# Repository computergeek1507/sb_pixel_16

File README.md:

# SBPixel16

A 16-port WS2812 pixel controller built on the **ESP32-P4**. It drives all 16 LED
strips simultaneously using the ESP32-P4's PARLIO peripheral for glitch-free parallel
DMA output. Pixel data comes from Ethernet (E1.31/sACN or DDP) or from **FSEQ
sequences played off a microSD card** in a standalone loop.

> **⚠️ WIP — Do not use.** Both the hardware and firmware are under active
> development and have not been fully validated.

This repository contains both the open-source **hardware** (KiCad 10) and the
**firmware** (Arduino / ESP-IDF).

---

## Features

- **16 parallel pixel outputs** — all strips clocked out together via PARLIO DMA,
  no RMT channel juggling.
- **Network input** — E1.31 (sACN, UDP 5568) or DDP (UDP 4048), selectable at runtime.
- **Standalone FSEQ playback** — plays uncompressed FSEQ v2 sequences (full or sparse)
  from a microSD card, looping the whole `/sequences` folder forever. No network needed.
- **Single-universe DMX512 output** — optional, generated on UART1 (250 kbaud, 8N2).
- **Web UI + REST API** — configure network, protocol, and per-port settings from a
  browser; config persists in LittleFS as `/config.json`.
- **On-OLED network setup** — set DHCP / static IP / gateway from the front-panel
  buttons, no computer required.
- **Over-the-air updates** — firmware and filesystem images can be flashed from the web UI.
- **Per-port configuration** — pixel count, start channel, color order, brightness,
  null/sacrificial pixels, and pixel grouping.
- **On-board 128×64 SSD1306 OLED** — shows IP, protocol, FPS, packet count, input
  voltages, SD status, and the currently playing sequence.
- **Two input-voltage monitors** — oversampled ADC readings (V1/V2) shown on the OLED.
- **Built-in test patterns** — cycle red / green / blue / rainbow with the on-board
  buttons; power-up RGB self-test on every boot.

---

## Repository layout

```
.
├── firmware/SBPixel16/     Arduino sketch (ESP32-P4)
│   ├── SBPixel16.ino        main app: setup/loop, config, Ethernet, parsers
│   ├── SBPixel16.h          board pin map & config structs
│   ├── parlio_ws2812.h      PARLIO parallel WS2812 DMA driver
│   ├── dmx_output.h         single-universe DMX512 output
│   ├── fseq_player.h        microSD FSEQ v2 player (uncompressed/sparse)
│   ├── net_menu.h           two-button OLED network editor
│   ├── data/                web UI source (packed into the LittleFS image)
│   └── page_*.h             web UI pages + REST API handlers
├── hardware/                KiCad 10 project (schematics, PCB, libraries)
│   └── ESP32-P4_16.*        board design files
└── LICENSE                  CC BY-NC 4.0 (firmware)
```

---

## Firmware

### Target

- **Board:** ESP32-P4 (Arduino-ESP32 3.x), e.g. Waveshare ESP32-P4-ETH
- **Ethernet PHY:** IP101GRI (RMII)
- **microSD:** the module's SDIO slot (4-bit) — used for FSEQ playback
- **Partition:** Default 4MB with SPIFFS (1.2 MB app / 1.5 MB filesystem)

### Required libraries

Install via the Arduino Library Manager:

| Library | Source |
| --- | --- |
| ESPAsyncWebServer | github.com/ESP32Async/ESPAsyncWebServer |
| AsyncTCP | github.com/ESP32Async/AsyncTCP |
| ArduinoJson | arduinojson.org |
| Adafruit GFX + Adafruit SSD1306 | Adafruit (OLED display) |

### Build & flash

1. Install the ESP32 board package (Arduino-ESP32 **3.x**) and select an **ESP32-P4** board.
2. **Enable PSRAM** (Tools → PSRAM → *Enabled* = `-DBOARD_HAS_PSRAM`). The module has
   PSRAM but the board default is *Disabled*, which leaves it uninitialized.
3. Set the partition scheme to **Default 4MB with SPIFFS**.
4. Open `firmware/SBPixel16/SBPixel16.ino`, compile, and upload.
5. Upload the web UI: flash the LittleFS filesystem image — a prebuilt
   `SBPixel16.littlefs.bin` is provided, or re-flash it over the air from the web UI.

On first boot with no `/config.json`, the firmware writes sensible defaults
(DHCP on, E1.31, 100 pixels/port, RGB order, 30% brightness).

**Board revisions:** the default build targets **HW1** (original pin map). Build for
the revised **HW2** board (pixel ports 12–16 rerouted off the USB pins onto
GPIO32/33/46/47/48) with `-DHW_VERSION=2`.

**Prebuilt binaries:** every push builds HW1 + HW2 firmware and the KiCad fabrication
outputs in CI — download them from the repo's **Actions** tab. When flashing over
serial after an OTA, use the `.merged.bin` (or first `esptool erase-region 0xe000
0x2000`), otherwise the bootloader keeps booting the previous OTA partition.

### REST API

| Method | Endpoint | Purpose |
| --- | --- | --- |
| GET | `/api/status` | Runtime stats (FPS, packet counts, voltages, SD/FSEQ status) |
| GET | `/api/config` | Current configuration as JSON |
| POST | `/api/config` | Update configuration |
| POST | `/api/reboot` | Reboot the controller |
| POST | `/api/ota/firmware` | Upload a firmware image |
| POST | `/api/ota/filesystem` | Upload a filesystem (web UI) image |

### Key defaults

- Refresh rate: ~40 fps (25 ms frame interval)
- Max pixels per port: 340 (configurable in `SBPixel16.h`)
- Input protocols: `0` = E1.31, `1` = DDP, `2` = FSEQ (SD card)
- Data timeout: outputs blank after 1 s with no packets
- E1.31 UDP port 5568 · DDP UDP port 4048 · HTTP port 80

### Front-panel controls (two buttons)

| Button | Action |
| --- | --- |
| **BTN1** tap | Cycle test pattern: Off → Red → Green → Blue → Rainbow → Off |
| **BTN2** tap | Stop the test pattern |
| **BTN2** hold (~1.5 s) | Open the `NETWORK SETUP` menu on the OLED |

**In the network menu:** **BTN1** changes the value under the cursor (hold to
auto-repeat), **BTN2** advances to the next field. Order: DHCP on/off → IP →
gateway → *Save & reboot*. Saving writes the config and reboots; 30 s of inactivity
cancels. Lets you set a static IP without a computer.

### FSEQ playback (microSD)

The microSD card is mounted at boot in every mode — its status shows on the OLED
(a card icon in the header) and the web dashboard. Set the input protocol to **FSEQ**
(Network page, or `protocol: 2`) to play from it: the controller scans **`/sequences`**
for `*.fseq` files, plays them alphabetically, and loops the whole folder forever — no
network connection required.

- **Format:** FSEQ v2, **uncompressed only** (full or sparse frames). Export from
  xLights / FPP with *No Compression*. Compressed files are skipped.
- **Channel mapping:** frame channels map to ports by each port's **Start Ch.**, exactly
  like E1.31/DDP — so brightness, color order, and grouping all still apply.
- The OLED and the web dashboard show the mounted card and the sequence now playing.

---

## Hardware

The board is a KiCad 10 open-hardware design (`hardware/ESP32-P4_16.*`) with 16 buffered
pixel outputs, dual power inputs with voltage monitoring, an SSD1306 OLED, two buttons,
and RMII Ethernet.

Design files, interactive BOM, and part list are published on the upstream project:

- **Interactive BOM:** https://computergeek1507.github.io/PB_16/ESP32-P4_16/bom/ibom
- **Part BOM (.ods):** https://github.com/computergeek1507/PB_16/raw/master/ESP32-P4_16/ESP32-P4_16_BOM.ods

---

## Licensing

Both the **firmware** and the **hardware** are licensed under **CC BY-NC 4.0**
(see [LICENSE](LICENSE)) — free to share and adapt for non-commercial use with
attribution.

Copyright © 2025 Scott Hanson.

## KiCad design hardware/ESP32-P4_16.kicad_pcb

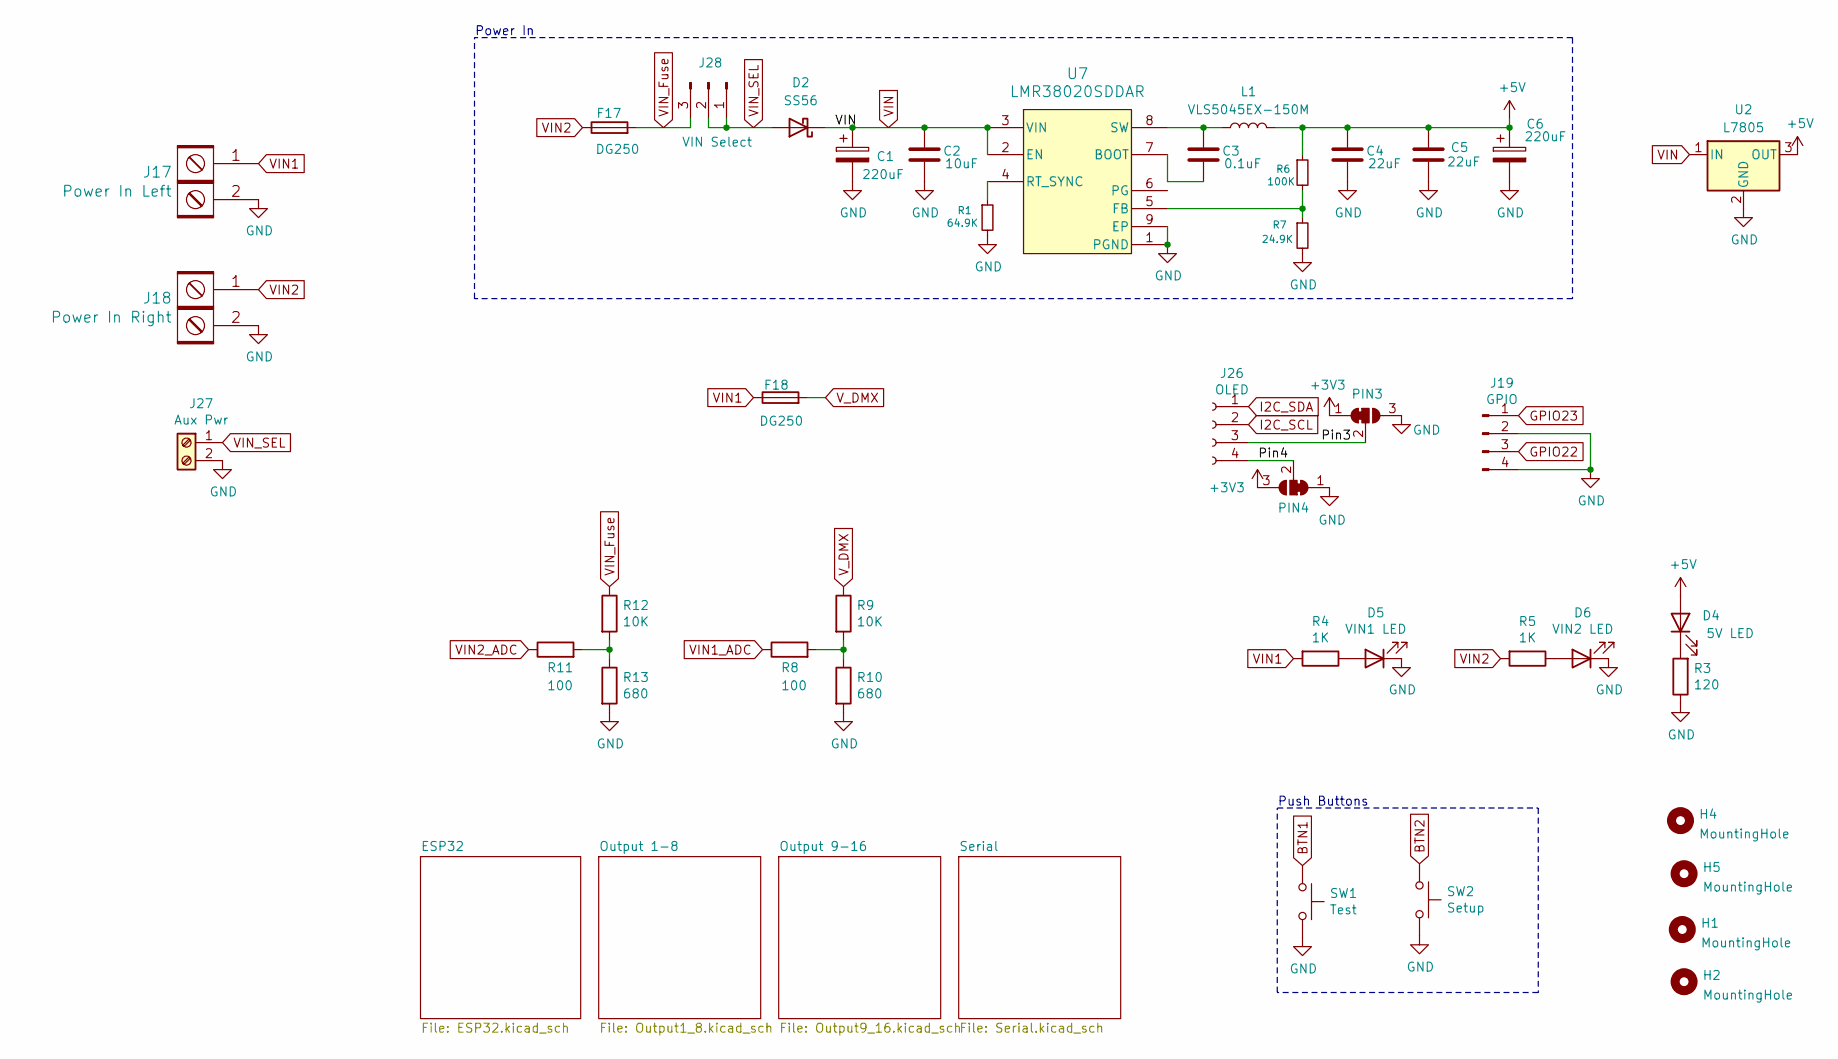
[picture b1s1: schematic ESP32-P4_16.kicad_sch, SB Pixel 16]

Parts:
C1, C6: 220uF; CP_Elec_8x10.5; LCSC C3340
C2: 10uF; C_1206_3216Metric; LCSC_PN C13585
C3: 0.1uF; C_0603_1608Metric; MPN CC0603KRX7R9BB104; LCSC C14663
C4, C5: 22uF; C_1206_3216Metric; LCSC_PN C1859
D2: SS56; D_SMA; LCSC C65009
D4: 5V LED; LED_0603_1608Metric; MPN LTST-C190KRKT; Digi-Key_PN 160-1436-2-ND
D5: VIN1 LED; LED_0603_1608Metric; MPN LTST-C190KRKT; Digi-Key_PN 160-1436-2-ND
D6: VIN2 LED; LED_0603_1608Metric; MPN LTST-C190KRKT; Digi-Key_PN 160-1436-2-ND
F17: DG250; Fuse_1812_4532Metric; MPN 3544-2
F18: DG250; Fuse_1812_4532Metric
H1, H2, H4, H5: MountingHole; MountingHole_3.7mm
J17: Power In Left; BARRIER_BLOCK_1ROW_2POS_P9.5MM; MPN OSTYK51102030; Digi-Key_PN ED2953-ND
J18: Power In Right; BARRIER_BLOCK_1ROW_2POS_P9.5MM; MPN OSTYK51102030; Digi-Key_PN ED2953-ND
J19: GPIO; JST_XH_B4B-XH-A_1x04_P2.50mm_Vertical; MPN B4B-XH-A(LF)(SN); Digi-Key_PN 455-2249-ND
J26: OLED; OLED-SSD1306-128X64-I2C-THT_2HOLE; MPN PPTC041LFBN-RC; Digi-Key_PN S7002-ND
J27: Aux Pwr; PHOENIX_MKDS1_2-3.81; MPN 1727010; Digi-Key_PN 277-1947-ND
J28: VIN Select; PinHeader_1x03_P2.54mm_Vertical; MPN 61300311121; Digi-Key_PN 732-5316-ND
L1: VLS5045EX-150M; IND_VLS5045EX-150M; MPN VLS5045EX-150M; Digi-Key_PN 445-174845-1-ND
PIN3: Jumper; SolderJumper-3_P1.3mm_Bridged12_Pad1.0x1.5mm
PIN4: JUMPER; SolderJumper-3_P1.3mm_Bridged12_Pad1.0x1.5mm
R1: 64.9K; R_0603_1608Metric; LCSC C14891
R3: 120; R_0603_1608Metric; MPN CRGCQ0603F120R; Digi-Key_PN A129677CT-ND
R4, R5: 1K; R_0603_1608Metric; MPN RC0603FR-071KL; Digi-Key_PN 311-1.00KHRTR-ND
R6: 100K; R_0603_1608Metric; LCSC C25803
R7: 24.9K; R_0603_1608Metric; LCSC C25962
R8, R11: 100; R_0603_1608Metric; MPN RMCF0603FT100R; Digi-Key_PN RMCF0603FT100RCT-ND
R9, R12: 10K; R_0603_1608Metric; MPN RC0603FR-0710KL; Digi-Key_PN 311-10.0KHRCT-ND
R10, R13: 680; R_0603_1608Metric; MPN RC0603FR-07680RL; Digi-Key_PN 311-680HRCT-ND
SW1: Test; SW_Push_1P1T_NO_6x6mm_H9.5mm; MPN PTS645SL50SMTR92 LFS; Digi-Key_PN CKN9088CT-ND
SW2: Setup; SW_Push_1P1T_NO_6x6mm_H9.5mm; MPN PTS645SL50SMTR92 LFS; Digi-Key_PN CKN9088CT-ND
U2: L7805; OKI-78SR_Horz
U7: LMR38020SDDAR; DDA0008E-IPC_A; MPN LMR38020SDDAR; Digi-Key_PN 296-LMR38020SDDARCT-ND

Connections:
+3V3: PIN3.1 (A), PIN4.3 (B); also elsewhere on the board
+5V: C4.1, C5.1, C6.1, D4.2 (A), L1.2, R6.1, U2.3 (OUT); also elsewhere on the board
/Pin3: J26.3, PIN3.2 (C)
/Pin4: J26.4, PIN4.2 (C)
BTN1: SW1.1; also elsewhere on the board
BTN2: SW2.1; also elsewhere on the board
GND: C1.2, C2.2, C4.2, C5.2, C6.2, D5.1 (K), D6.1 (K), J17.2, J18.2, J19.2, J19.4, J27.2, PIN3.3 (B), PIN4.1 (A), R1.2, R3.1, R7.2, R10.2, R13.2, SW1.2, SW2.2, U2.2 (GND), U7.1 (PGND), U7.9 (EP); also elsewhere on the board
GPIO22: J19.3; also elsewhere on the board
GPIO23: J19.1; also elsewhere on the board
I2C_SCL: J26.2; also elsewhere on the board
I2C_SDA: J26.1; also elsewhere on the board
unnamed: D4.1 (K), R3.2
unnamed: D5.2 (A), R4.1
unnamed: D6.2 (A), R5.1
unnamed: R8.2, R9.2, R10.1
unnamed: R11.2, R12.2, R13.1
unnamed: C3.2, U7.7 (BOOT)
unnamed: R6.2, R7.1, U7.5 (FB)
unnamed: R1.1, U7.4 (RT_SYNC)
unnamed: C3.1, L1.1, U7.8 (SW)
VIN: C1.1, C2.1, D2.1 (K), U2.1 (IN), U7.2 (EN), U7.3 (VIN)
VIN1: F18.1, J17.1, R4.2; also elsewhere on the board
VIN1_ADC: R8.1; also elsewhere on the board
VIN2: F17.1, J18.1, R5.2; also elsewhere on the board
VIN2_ADC: R11.1; also elsewhere on the board
VIN_Fuse: F17.2, J28.3, R12.1
VIN_SEL: D2.2 (A), J27.1, J28.1, J28.2
V_DMX: F18.2, R9.1; also elsewhere on the board

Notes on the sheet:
Push Buttons
Power In

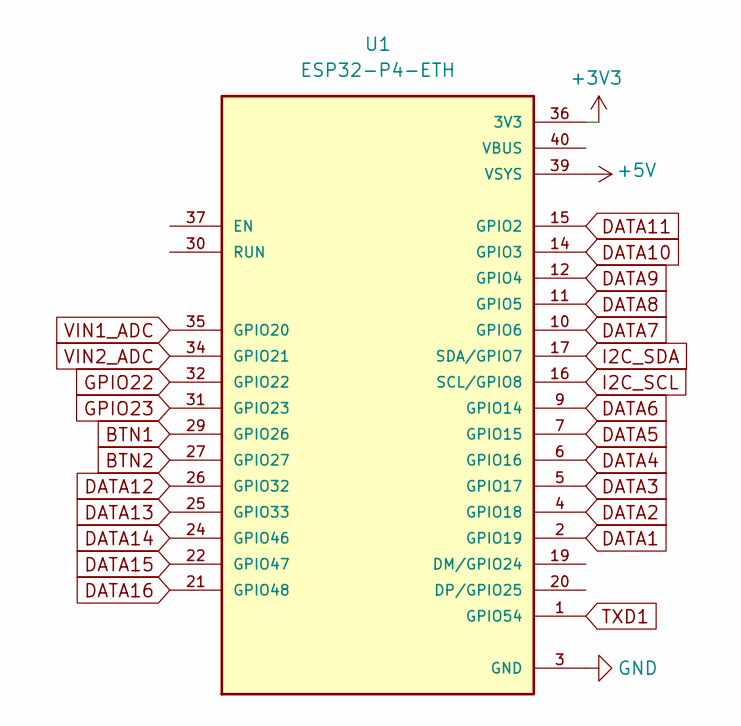
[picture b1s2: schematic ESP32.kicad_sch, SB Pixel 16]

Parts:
U1: ESP32-P4-ETH; MODULE_ESP32-P4-ETH

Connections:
+3V3: U1.36 (3V3); also elsewhere on the board
+5V: U1.39 (VSYS); also elsewhere on the board
BTN1: U1.29 (GPIO26); also elsewhere on the board
BTN2: U1.27 (GPIO27); also elsewhere on the board
DATA1: U1.2 (GPIO19); also elsewhere on the board
DATA2: U1.4 (GPIO18); also elsewhere on the board
DATA3: U1.5 (GPIO17); also elsewhere on the board
DATA4: U1.6 (GPIO16); also elsewhere on the board
DATA5: U1.7 (GPIO15); also elsewhere on the board
DATA6: U1.9 (GPIO14); also elsewhere on the board
DATA7: U1.10 (GPIO6); also elsewhere on the board
DATA8: U1.11 (GPIO5); also elsewhere on the board
DATA9: U1.12 (GPIO4); also elsewhere on the board
DATA10: U1.14 (GPIO3); also elsewhere on the board
DATA11: U1.15 (GPIO2); also elsewhere on the board
DATA12: U1.26 (GPIO32); also elsewhere on the board
DATA13: U1.25 (GPIO33); also elsewhere on the board
DATA14: U1.24 (GPIO46); also elsewhere on the board
DATA15: U1.22 (GPIO47); also elsewhere on the board
DATA16: U1.21 (GPIO48); also elsewhere on the board
GND: U1.3 (GND), U1.8 (GND), U1.13 (GND), U1.18 (GND), U1.23 (GND), U1.28 (GND), U1.33 (GND), U1.38 (GND); also elsewhere on the board
GPIO22: U1.32 (GPIO22); also elsewhere on the board
GPIO23: U1.31 (GPIO23); also elsewhere on the board
I2C_SCL: U1.16 (SCL/GPIO8); also elsewhere on the board
I2C_SDA: U1.17 (SDA/GPIO7); also elsewhere on the board
TXD1: U1.1 (GPIO54); also elsewhere on the board
VIN1_ADC: U1.35 (GPIO20); also elsewhere on the board
VIN2_ADC: U1.34 (GPIO21); also elsewhere on the board

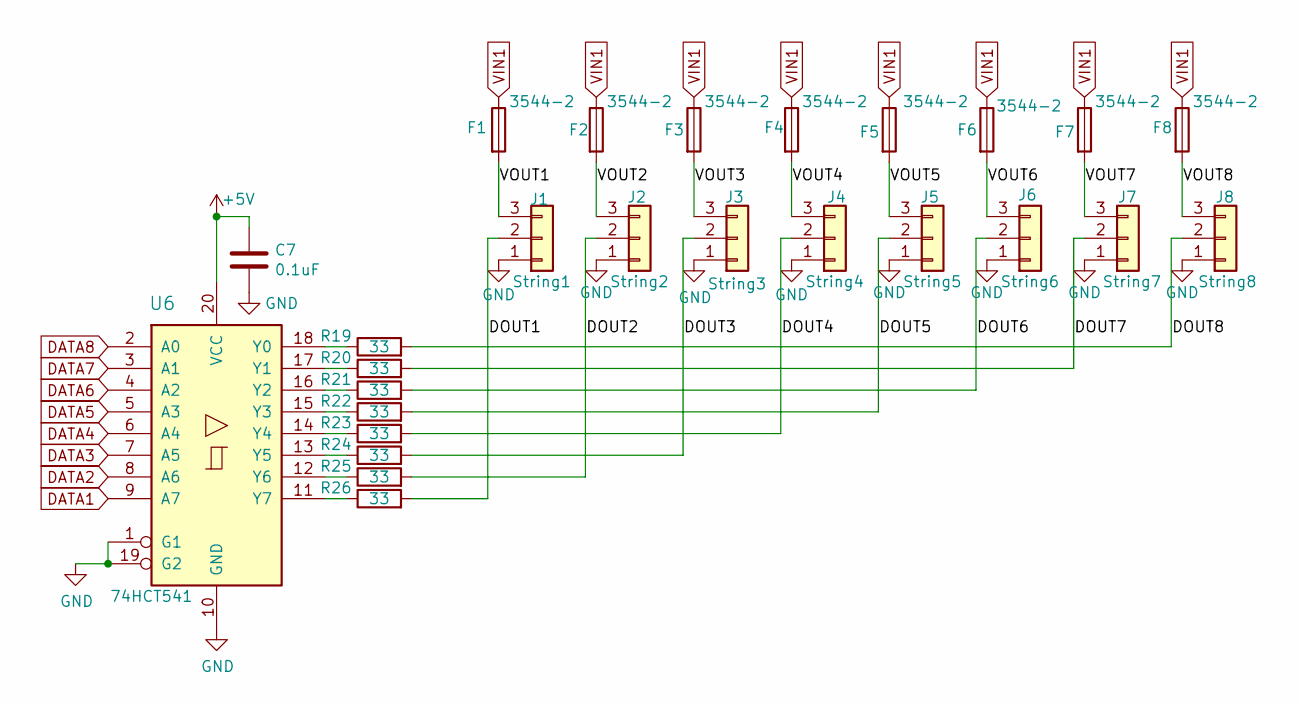
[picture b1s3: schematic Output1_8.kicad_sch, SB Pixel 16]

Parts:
C7: 0.1uF; C_0603_1608Metric; MPN CL10B104KB8NNWC; Digi-Key_PN 1276-1935-2-ND
F1, F2, F3, F4, F5, F6, F7, F8: 3544-2; Fuse_1812_4532Metric; MPN 3544-2
J1: String1; PHOENIX_1864299_1; MPN 1843619/OSTTJ0311530
J2: String2; PHOENIX_1864299_1; MPN 1843619/OSTTJ0311530
J3: String3; PHOENIX_1864299_1; MPN 1843619/OSTTJ0311530
J4: String4; PHOENIX_1864299_1; MPN 1843619/OSTTJ0311530
J5: String5; PHOENIX_1864299_1; MPN 1843619/OSTTJ0311530
J6: String6; PHOENIX_1864299_1; MPN 1843619/OSTTJ0311530
J7: String7; PHOENIX_1864299_1; MPN 1843619/OSTTJ0311530
J8: String8; PHOENIX_1864299_1; MPN 1843619/OSTTJ0311530
R19, R20, R21, R22, R23, R24, R25, R26: 33; R_0603_1608Metric; MPN CN34J330CT; LCSC C23140
U6: 74HCT541; TSSOP-20_4.4x6.5mm_P0.65mm; MPN SN74HCT541PWR; Digi-Key_PN MC74HCT541ADTR2GOSTR-ND

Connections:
+5V: C7.1, U6.20 (VCC); also elsewhere on the board
/Output 1-8/DOUT1: J1.2, R26.2
/Output 1-8/DOUT2: J2.2, R25.2
/Output 1-8/DOUT3: J3.2, R24.2
/Output 1-8/DOUT4: J4.2, R23.2
/Output 1-8/DOUT5: J5.2, R22.2
/Output 1-8/DOUT6: J6.2, R21.2
/Output 1-8/DOUT7: J7.2, R20.2
/Output 1-8/DOUT8: J8.2, R19.2
/Output 1-8/VOUT1: F1.2, J1.3
/Output 1-8/VOUT2: F2.2, J2.3
/Output 1-8/VOUT3: F3.2, J3.3
/Output 1-8/VOUT4: F4.2, J4.3
/Output 1-8/VOUT5: F5.2, J5.3
/Output 1-8/VOUT6: F6.2, J6.3
/Output 1-8/VOUT7: F7.2, J7.3
/Output 1-8/VOUT8: F8.2, J8.3
DATA1: U6.9 (A7); also elsewhere on the board
DATA2: U6.8 (A6); also elsewhere on the board
DATA3: U6.7 (A5); also elsewhere on the board
DATA4: U6.6 (A4); also elsewhere on the board
DATA5: U6.5 (A3); also elsewhere on the board
DATA6: U6.4 (A2); also elsewhere on the board
DATA7: U6.3 (A1); also elsewhere on the board
DATA8: U6.2 (A0); also elsewhere on the board
GND: C7.2, J1.1, J2.1, J3.1, J4.1, J5.1, J6.1, J7.1, J8.1, U6.1 (G1), U6.10 (GND), U6.19 (G2); also elsewhere on the board
unnamed: R19.1, U6.18 (Y0)
unnamed: R20.1, U6.17 (Y1)
unnamed: R21.1, U6.16 (Y2)
unnamed: R22.1, U6.15 (Y3)
unnamed: R23.1, U6.14 (Y4)
unnamed: R24.1, U6.13 (Y5)
unnamed: R25.1, U6.12 (Y6)
unnamed: R26.1, U6.11 (Y7)
VIN1: F1.1, F2.1, F3.1, F4.1, F5.1, F6.1, F7.1, F8.1; also elsewhere on the board

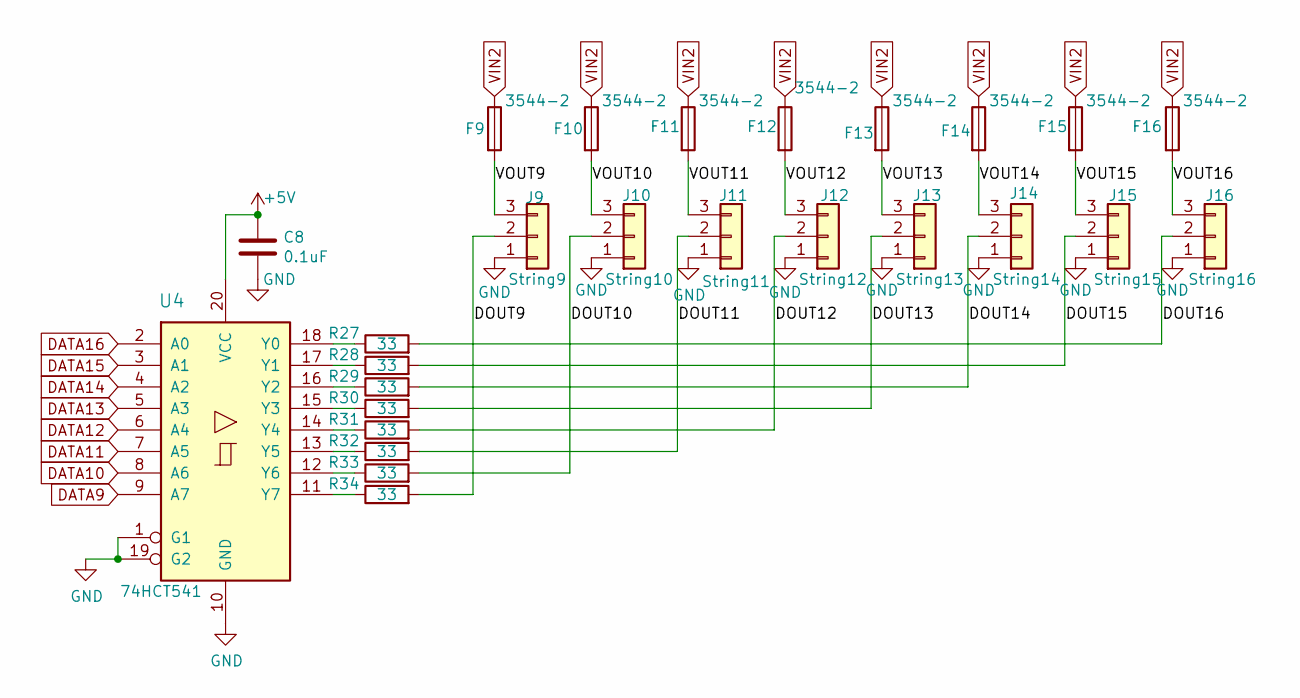
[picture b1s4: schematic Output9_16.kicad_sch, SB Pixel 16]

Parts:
C8: 0.1uF; C_0603_1608Metric; MPN CL10B104KB8NNWC; Digi-Key_PN 1276-1935-2-ND
F9, F10, F11, F12, F13, F14, F15, F16: 3544-2; Fuse_1812_4532Metric; MPN 3544-2
J9: String9; PHOENIX_1864299_1; MPN 1843619/OSTTJ0311530
J10: String10; PHOENIX_1864299_1; MPN 1843619/OSTTJ0311530
J11: String11; PHOENIX_1864299_1; MPN 1843619/OSTTJ0311530
J12: String12; PHOENIX_1864299_1; MPN 1843619/OSTTJ0311530
J13: String13; PHOENIX_1864299_1; MPN 1843619/OSTTJ0311530
J14: String14; PHOENIX_1864299_1; MPN 1843619/OSTTJ0311530
J15: String15; PHOENIX_1864299_1; MPN 1843619/OSTTJ0311530
J16: String16; PHOENIX_1864299_1; MPN 1843619/OSTTJ0311530
R27, R28, R29, R30, R31, R32, R33, R34: 33; R_0603_1608Metric; MPN CN34J330CT; LCSC C23140
U4: 74HCT541; TSSOP-20_4.4x6.5mm_P0.65mm; MPN SN74HCT541PWR; Digi-Key_PN MC74HCT541ADTR2GOSTR-ND

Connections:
+5V: C8.1, U4.20 (VCC); also elsewhere on the board
/Output 9-16/DOUT9: J9.2, R34.2
/Output 9-16/DOUT10: J10.2, R33.2
/Output 9-16/DOUT11: J11.2, R32.2
/Output 9-16/DOUT12: J12.2, R31.2
/Output 9-16/DOUT13: J13.2, R30.2
/Output 9-16/DOUT14: J14.2, R29.2
/Output 9-16/DOUT15: J15.2, R28.2
/Output 9-16/DOUT16: J16.2, R27.2
/Output 9-16/VOUT9: F9.2, J9.3
/Output 9-16/VOUT10: F10.2, J10.3
/Output 9-16/VOUT11: F11.2, J11.3
/Output 9-16/VOUT12: F12.2, J12.3
/Output 9-16/VOUT13: F13.2, J13.3
/Output 9-16/VOUT14: F14.2, J14.3
/Output 9-16/VOUT15: F15.2, J15.3
/Output 9-16/VOUT16: F16.2, J16.3
DATA9: U4.9 (A7); also elsewhere on the board
DATA10: U4.8 (A6); also elsewhere on the board
DATA11: U4.7 (A5); also elsewhere on the board
DATA12: U4.6 (A4); also elsewhere on the board
DATA13: U4.5 (A3); also elsewhere on the board
DATA14: U4.4 (A2); also elsewhere on the board
DATA15: U4.3 (A1); also elsewhere on the board
DATA16: U4.2 (A0); also elsewhere on the board
GND: C8.2, J9.1, J10.1, J11.1, J12.1, J13.1, J14.1, J15.1, J16.1, U4.1 (G1), U4.10 (GND), U4.19 (G2); also elsewhere on the board
unnamed: R27.1, U4.18 (Y0)
unnamed: R28.1, U4.17 (Y1)
unnamed: R29.1, U4.16 (Y2)
unnamed: R30.1, U4.15 (Y3)
unnamed: R31.1, U4.14 (Y4)
unnamed: R32.1, U4.13 (Y5)
unnamed: R33.1, U4.12 (Y6)
unnamed: R34.1, U4.11 (Y7)
VIN2: F9.1, F10.1, F11.1, F12.1, F13.1, F14.1, F15.1, F16.1; also elsewhere on the board

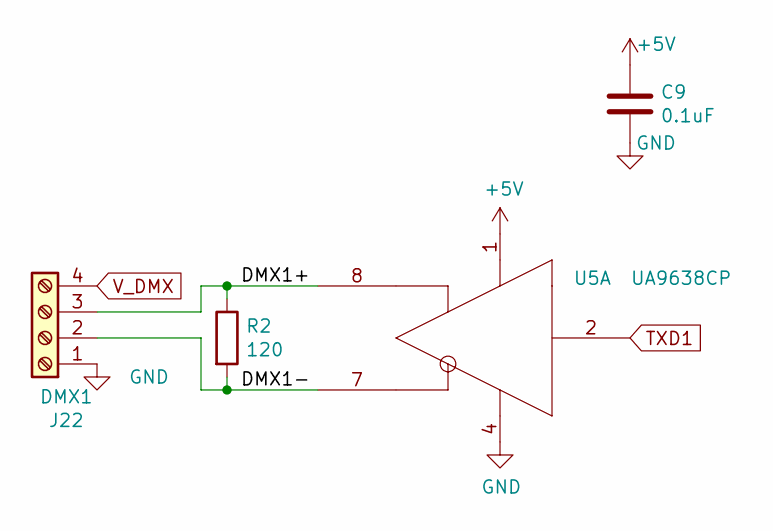
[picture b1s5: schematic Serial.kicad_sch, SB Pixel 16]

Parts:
C9: 0.1uF; C_0603_1608Metric; MPN CL10B104KB8NNWC; Digi-Key_PN 1276-1935-2-ND
J22: DMX1; TerminalBlock_Phoenix_MKDS-1,5-4_1x04_P5.00mm_Horizontal; MPN 1729034; Digi-Key_PN 277-1238-ND
R2: 120; R_0603_1608Metric; MPN CRGCQ0603F120R; Digi-Key_PN A129677CT-ND
U5: UA9638CP; SOIC-8_3.9x4.9mm_P1.27mm; MPN UA9638CDR; Digi-Key_PN UA9638CP

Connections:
+5V: C9.1, U5.1 (VCC); also elsewhere on the board
/Serial/DMX1+: J22.3, R2.1, U5.8 (OUTB)
/Serial/DMX1-: J22.2, R2.2, U5.7 (OUTA)
GND: C9.2, J22.1, U5.4 (GND); also elsewhere on the board
TXD1: U5.2 (IN); also elsewhere on the board
V_DMX: J22.4; also elsewhere on the board

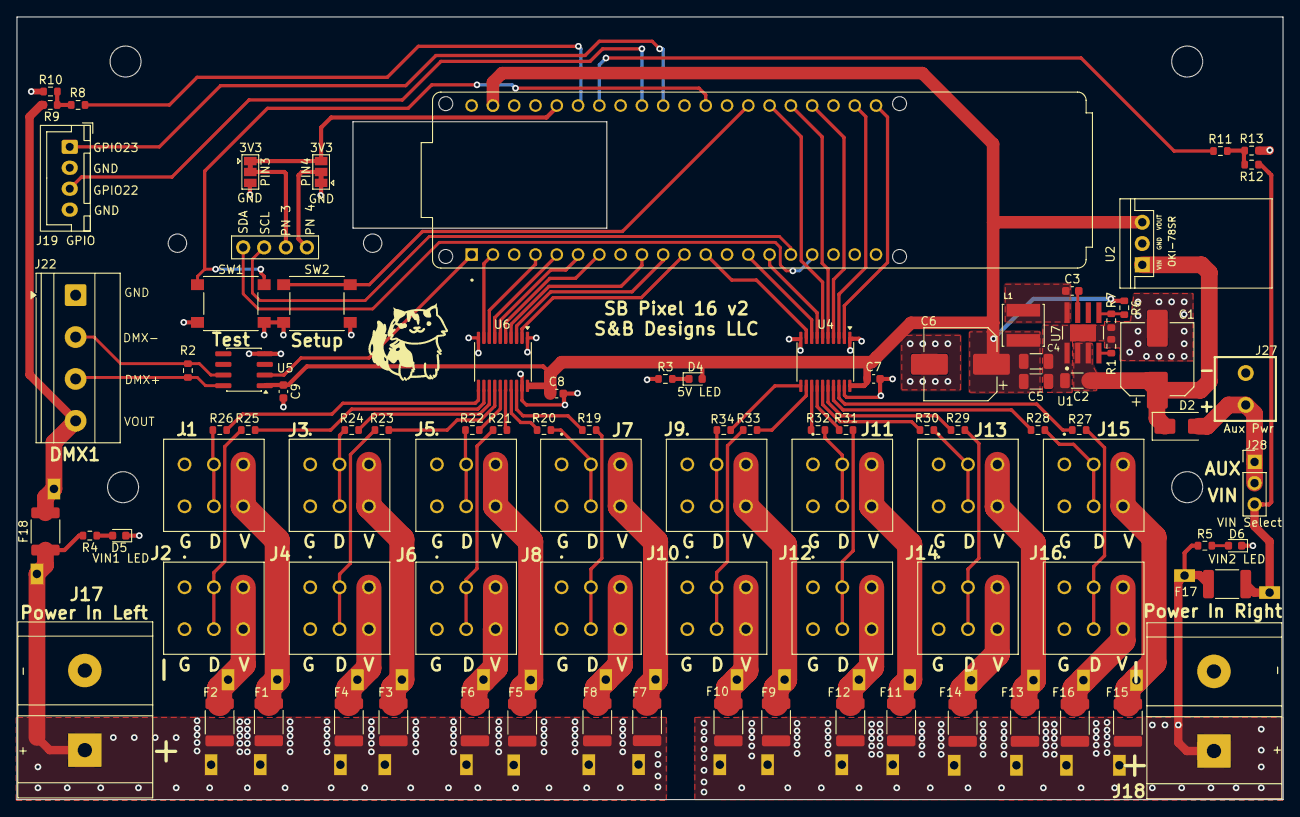
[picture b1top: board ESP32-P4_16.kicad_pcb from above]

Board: 2 copper layers, 151.1 x 93.4 mm, 98 parts (0 on the bottom side), 95 nets.

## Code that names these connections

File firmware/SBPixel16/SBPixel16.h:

#pragma once

// ── Firmware version ──────────────────────────────────────────────────────────
#define FW_VERSION    "1.0.0"                 // semantic version (bump on release)
#define FW_BUILD      17                      // build number (bump each flashed build)
#define FW_BUILD_DATE (__DATE__ " " __TIME__) // compile timestamp = unique build id

// ── Board / port constants ────────────────────────────────────────────────────

#define NUM_PORTS       16
#define MAX_PIXELS      340     // max pixels per port; increase if needed (affects FPS)
#define DATA_TIMEOUT    1000    // ms before clearing pixels on no data
#define REFRESH         25      // ms between FastLED.show() calls (~40fps target)
#define PORT_CYCLE_MS   2000    // port-cycle test: ms each port stays lit
#define HTTP_PORT       80
#define E131_UDP_PORT   5568
#define DDP_UDP_PORT    4048
#define CONFIG_FILE     "/config.json"

// ── GPIO output pins for the 16 pixel ports ───────────────────────────────────
// Pin assignments taken directly from the board schematic DATA1–DATA16 labels.
// NOTE: DATA14=GPIO24 (USB DM) and DATA16=GPIO25 (USB DP) — using these for
// pixel output disables USB on-the-fly; acceptable since USB is not needed here.
#define PIN_P0   19   // DATA1
#define PIN_P1   18   // DATA2
#define PIN_P2   17   // DATA3
#define PIN_P3   16   // DATA4
#define PIN_P4   15   // DATA5
#define PIN_P5   14   // DATA6
#define PIN_P6    6   // DATA7
#define PIN_P7    5   // DATA8
#define PIN_P8    4   // DATA9
#define PIN_P9    3   // DATA10
#define PIN_P10   2   // DATA11

// ── Board revision: pixel ports 12-16 (PIN_P11..PIN_P15) differ per HW rev ─────
// HW1 = original board.  HW2 = revised board that reroutes ports 12-16 (notably
// 14 & 16 off the USB pins GPIO24/25).  Build HW2 with -DHW_VERSION=2, or change
// the default below.
#ifndef HW_VERSION
#define HW_VERSION  1
#endif

#if HW_VERSION >= 2
  // ---- HW2 (revised board): ports 12-16 remapped off the USB pins ----
  #define PIN_P11  32   // DATA12  (port 12)  was GPIO46
  #define PIN_P12  33   // DATA13  (port 13)  was GPIO47
  #define PIN_P13  46   // DATA14  (port 14)  was GPIO24 (USB DM)
  #define PIN_P14  47   // DATA15  (port 15)  was GPIO48
  #define PIN_P15  48   // DATA16  (port 16)  was GPIO25 (USB DP)
#else
  // ---- HW1 (original board) ----
  #define PIN_P11  46   // DATA12
  #define PIN_P12  47   // DATA13
  #define PIN_P13  24   // DATA14  (USB DM — dead on HW1)
  #define PIN_P14  48   // DATA15
  #define PIN_P15  25   // DATA16  (USB DP — dead on HW1)
#endif

// ── Ethernet PHY (IP101GRI on Waveshare ESP32-P4-ETH) ─────────────────────────
#define ETH_PHY_TYPE    ETH_PHY_IP101
#define ETH_PHY_ADDR    1
#define ETH_PHY_MDC     31
#define ETH_PHY_MDIO    52
#define ETH_PHY_POWER   51      // PHY reset / power-enable
#define ETH_CLK_MODE    EMAC_CLK_EXT_IN  // 50 MHz ext crystal → GPIO50

// ── OLED (SSD1306 128×64, I2C) ───────────────────────────────────────────────
// Uses the Waveshare board's default I2C bus.
#define OLED_SDA    7
#define OLED_SCL    8
#define OLED_ADDR   0x3C
#define OLED_W      128
#define OLED_H      64

// ── microSD (SDIO 4-bit, on the ESP32-P4-ETH module) ──────────────────────────
// Card slot lives on the Waveshare module, not the SBPixel16 PCB. SDMMC signals:
#define SD_CLK_PIN  43
#define SD_CMD_PIN  44
#define SD_D0_PIN   39
#define SD_D1_PIN   40
#define SD_D2_PIN   41
#define SD_D3_PIN   42
#define SD_PWR_PIN  45      // Q1 high-side P-FET: drive LOW to power the card
#define FSEQ_DIR    "/sequences"   // sequences played in a loop from here
#define SD_CONFIG_FILE "/config.json"   // optional config override, SD card root

// ── ADC inputs ────────────────────────────────────────────────────────────────
#define VIN1_PIN    20   // VIN1_ADC
#define VIN2_PIN    21   // VIN2_ADC
#define ADC_SAMPLES  8   // oversampling count for noise reduction
// VIN sense divider (per schematic): VINx --[10k]-- node --[680]-- GND,
// node --[100]-- ADC pin. Actual VIN = pin_mV * (10000+680)/680.
#define VIN_DIV_NUM  10680
#define VIN_DIV_DEN  680

// ── Buttons ───────────────────────────────────────────────────────────────────
#define BTN1_PIN    26   // test-cycle button (active LOW, internal pull-up)
#define BTN2_PIN    27   // test-stop  button (active LOW, internal pull-up)
#define BTN_DEBOUNCE_MS  50
#define LONGPRESS_MS    1500   // hold BTN1 this long to open the OLED network menu
#define REPEAT_DELAY_MS  500   // hold-to-repeat: delay before auto-repeat starts
#define REPEAT_RATE_MS   120   // hold-to-repeat: interval between repeats

// ── Pixel output limits ───────────────────────────────────────────────────────
#define MAX_NULL_PIXELS  50    // max null/sacrificial pixels per port
#define MAX_GROUPING      8    // max physical LEDs per logical channel group

// ── Color order (wire order of the physical LED) ──────────────────────────────
// FastLED NEOPIXEL sends bytes as G,R,B. These constants drive the permutation
// that makes each physical LED type receive the correct byte sequence.
#define CO_GRB  0   // WS2812 / WS2811 default
#define CO_RGB  1
#define CO_BGR  2
#define CO_RBG  3
#define CO_GBR  4
#define CO_BRG  5

// ── Input protocol ────────────────────────────────────────────────────────────
#define PROTO_E131  0
#define PROTO_DDP   1
#define PROTO_FSEQ  2   // play FSEQ files from microSD in an endless loop

// ── Config structs ────────────────────────────────────────────────────────────

typedef struct {
    uint16_t pixelCount;    // logical pixel count (unique channel groups)
    uint32_t startChannel;  // absolute 1-based channel index
    uint8_t  colorOrder;    // CO_GRB … CO_BRG (default CO_GRB = 0)
    uint8_t  nullPixels;    // sacrificial pixels sent before data (0–MAX_NULL_PIXELS)
    uint8_t  grouping;      // physical LEDs per logical pixel (1 = no grouping)
    uint8_t  brightness;    // per-port output brightness, percent (0-100)
} PortConfig;

typedef struct {
    bool     dhcp      = false;
    String   ip        = "192.168.1.200";
    String   subnet    = "255.255.255.0";
    String   gateway   = "192.168.1.1";
    uint8_t  protocol  = PROTO_E131;
    uint16_t uniStart  = 1;
    uint16_t uniSize   = 510;
    PortConfig ports[NUM_PORTS];
    // DMX output
    bool     dmxEnabled  = false;
    uint32_t dmxStartCh  = 1;
    uint16_t dmxChannels = 512;

#define DMX_TX_PIN 54
} AppConfig;

// ── Runtime stats (updated in loop) ──────────────────────────────────────────
extern uint32_t g_e131Packets;
extern uint32_t g_ddpPackets;
extern uint32_t g_fps;
extern uint32_t g_lastPacket;

// ADC readings (millivolts, updated every 500 ms)
extern uint32_t g_vin1_mv;
extern uint32_t g_vin2_mv;

// Test mode: 0=off 1=red 2=green 3=blue 4=rainbow 5=port-cycle
extern uint8_t  g_testMode;
extern uint8_t  g_testPort;   // active port (0-based) in the port-cycle test

// True if the PARLIO WS2812 driver initialized OK (else pixel output is dead).
extern bool g_parlioOk;

// Diagnostics surfaced in /api/status for remote debugging.
extern volatile bool     g_menuActive;   // OLED network menu currently open
extern volatile uint32_t g_b1HeldMs;     // how long BTN1 has been held (0 = up)

// OTA in progress: loop() suspends pixel rendering so the async web-server
// task gets the CPU and an uncontended flash bus (fixes slow/failing uploads).
extern volatile bool     g_otaActive;
extern volatile uint32_t g_otaLastMs;
extern volatile uint32_t g_otaFlashMs;   // duration of the last PSRAM->flash write
extern volatile uint8_t  g_otaMode;      // last OTA buffer path: 0=idle 1=psram 2=stream

// microSD / FSEQ playback status (surfaced on OLED + web dashboard)
extern bool     g_sdMounted;
extern uint32_t g_sdSizeMB;
extern uint16_t g_fseqCount;    // playable sequences found in FSEQ_DIR
extern char     g_sdError[24];  // SD mount result/how (diagnostic)
extern uint32_t g_fseqFrame;    // current frame of the playing sequence
extern uint32_t g_fseqFrames;   // total frames in the playing sequence
extern char     g_fseqName[32]; // file name currently playing

// ── Global config ─────────────────────────────────────────────────────────────
extern AppConfig cfg;
